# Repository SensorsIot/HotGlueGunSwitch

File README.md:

# HotGlueGunSwitch
Timer for Hot Glue Guns

Description of the project on Youtube: https://youtu.be/2SVzzAe2HBY

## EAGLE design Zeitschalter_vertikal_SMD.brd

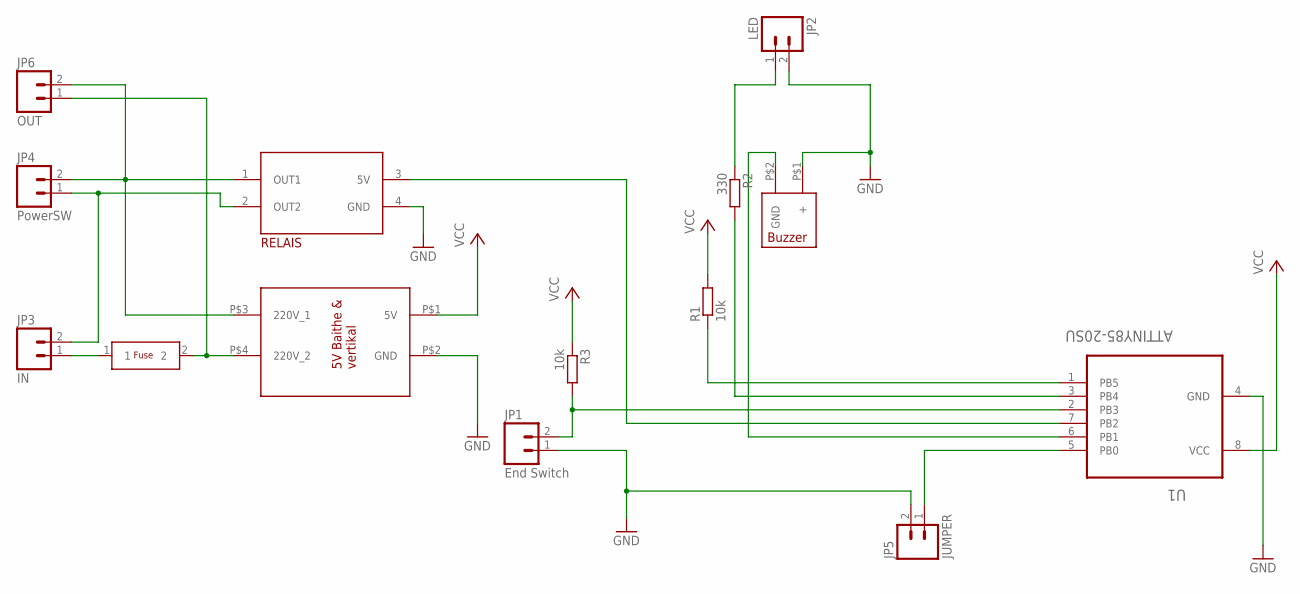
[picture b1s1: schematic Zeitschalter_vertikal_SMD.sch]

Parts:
FUSE: FUSE; FUSE_RESETABLE
JP1: End Switch; 1X02_LOCK_LONGPADS
JP2: LED; 1X02_LOCK_LONGPADS
JP3: IN; SCREWTERMINAL-5MM-2
JP4: PowerSW; 1X02_LOCK_LONGPADS
JP5: JUMPER; 1X02_LOCK_LONGPADS
JP6: OUT; SCREWTERMINAL-5MM-2
R1, R3: 10k; M1206
R2: 330; M1206
U1: ATTINY85-20SU; SOIC127P798X216-8N
U$1: NETZTEIL_VERTIKAL_5V
U$2: OMRON-G3MB-202P
U$3: BUZZER

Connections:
GND: JP1.1, JP2.2, JP5.2, U1.4 (GND), U$1.P$2 (GND), U$2.4 (GND), U$3.P$1 (+)
unnamed: FUSE.1, JP3.1
unnamed: JP4.2, JP6.2, U$1.P$3 (220V_1), U$2.1 (OUT1)
unnamed: R2.2, U1.3 (PB4)
unnamed: JP1.2, R3.2, U1.2 (PB3)
unnamed: JP5.1, U1.5 (PB0)
unnamed: FUSE.2, JP6.1, U$1.P$4 (220V_2)
unnamed: R1.1, U1.1 (PB5)
unnamed: JP2.1, R2.1
unnamed: U1.6 (PB1), U$3.P$2 (GND)
unnamed: U1.7 (PB2), U$2.3 (5V)
unnamed: JP3.2, JP4.1, U$2.2 (OUT2)
VCC: R1.2, R3.1, U1.8 (VCC), U$1.P$1 (5V)

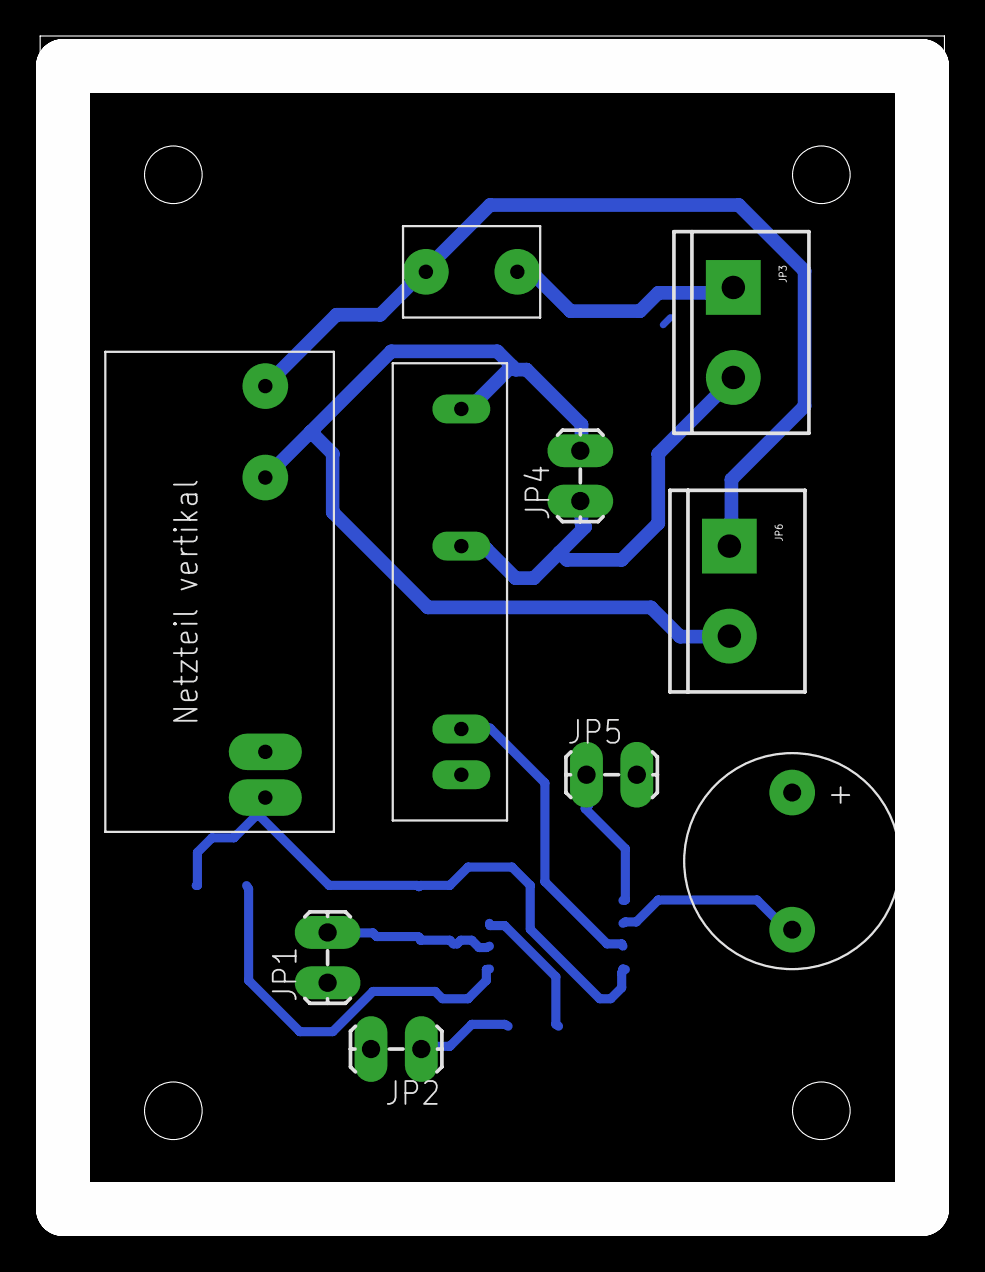
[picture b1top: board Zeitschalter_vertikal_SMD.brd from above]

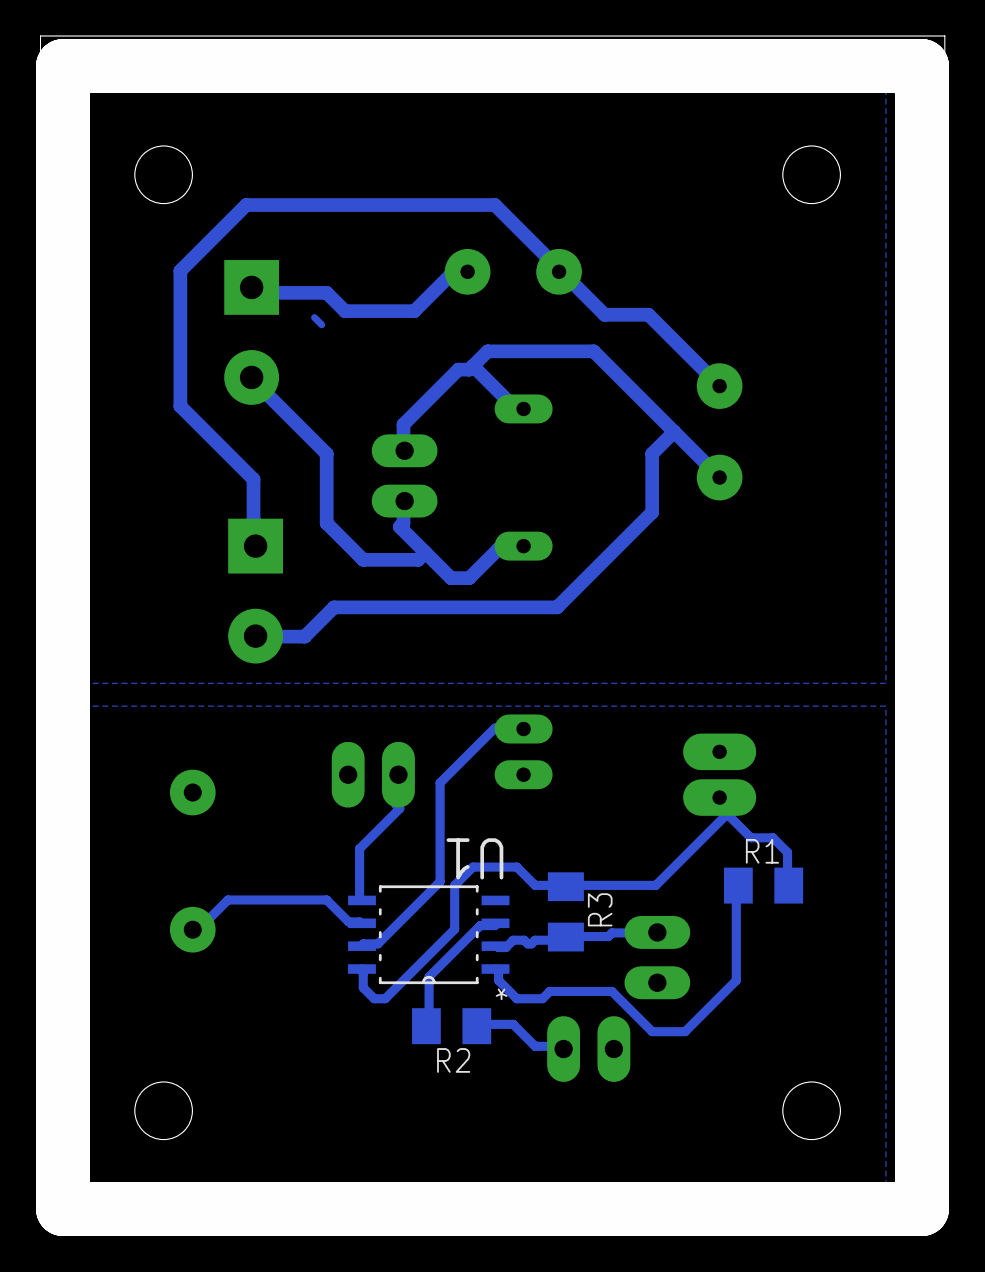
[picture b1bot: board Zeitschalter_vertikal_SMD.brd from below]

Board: 2 copper layers, 50.2 x 65.7 mm, 14 parts (4 on the bottom side), 13 nets.

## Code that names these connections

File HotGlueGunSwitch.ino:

/*
  HotGlueSwitch

  This timer turns an Hot Glue Gun or any other appliance on for a time (timer2) and switches it off afterwards.
  For Hot Glue guns a "readiness warning can be built in: after a time timer1  a beeper announces for READY_DURATION, that the temperature should be ok to start working.
  Before the timer2 switches the gun off it warns for WARNING_DURATION. During this time, pressing the button extends the time for another timer2 duration.

  It runs on an ATTINY85

  This example code is in the public domain.

  published August, 1st 2015 by Andreas Spiess
 */
 
#include <avr/io.h>
#include <EEPROM.h>


#define SW_OPEN     HIGH
#define SW_CLOSED   LOW
#define OUT_ON		HIGH
#define OUT_OFF		LOW

#define FACTOR 1000


// Pin1 RESET  #define DEBUG1 PB5 // Pin1, nur mit Fuse change

#define SWITCH PB3   // Pin2

#define LED    PB4    // Pin3
// Pin4 GND
#define PROGRAMMER PB0    // Pin5
#define BUZZER PB1   // Pin6
#define RELAIS PB2    // Pin7
// Pin8 VCC

const int timer2 = 600;   // 600 sec = 10min
const int timer1 = 140; // 140 sec (until glue is hot enough;
const int WARNING_DURATION = 60;  // 60sec;
const int READY_DURATION = 3;   // 3 sec

byte status = 1;
long timeStat;

void setup() {
  pinMode(SWITCH, INPUT_PULLUP);
  pinMode(LED, OUTPUT);
  pinMode(PROGRAMMER, INPUT);
  pinMode(BUZZER, OUTPUT);
  pinMode(RELAIS, OUTPUT);
  digitalWrite(SWITCH, HIGH); //
  digitalWrite(LED, OUT_OFF); //
  digitalWrite(BUZZER, OUT_OFF); //
  digitalWrite(RELAIS, OUT_ON); //
  timeStat = millis();
  delay(200);

}


void loop () {
  switch (status) {

    case 1:
      // Appliance on
      digitalWrite(RELAIS, OUT_ON);
      digitalWrite(LED, OUT_ON);
      if (timeOut(timeStat, timer1))  status = 5; // Appliance ready
      break;

    case 2:
      // Warning
      beep(200);
      smartDelay(2000);
      if (keyPressed())  status = 3;
      if (timeOut(timeStat, timer2)) status = 4;  // Appliance off
      break;

    case 3:
      // Time Extension
      timeStat = millis();   // reset timer to start duration over
      for (int ii = 0; ii < 3; ii++) {   ///three beeps for confirmation
        beep(100);
        delay(100);
      }
      timeStat = millis();
      status = 6;
      break;

    case 4:
      // Appliance off
      digitalWrite(RELAIS, OUT_OFF);
      digitalWrite(LED, OUT_OFF);
      digitalWrite(BUZZER, OUT_OFF);
      while (1 == 1);  // wait forever
      break;

    case 5:
      // Appliance ready
      digitalWrite(RELAIS, OUT_ON);
      digitalWrite(LED, OUT_ON);
      beep(200);
      smartDelay(100);
      if (timeOut(timeStat, (timer1 + READY_DURATION))) status = 6;
      if (keyPressed()) status = 3;   // time extension
      break;

    case 6:
      // Status after Appliance ready: Appliance still on, but no more warning for readiness
      digitalWrite(RELAIS, OUT_ON);
      digitalWrite(LED, OUT_ON);
      if (timeOut(timeStat, timer2 - WARNING_DURATION)) status = 2;
      if (keyPressed()) status = 3;   // time extension
      break;

    default:  // should never happen...
      status = 1;
      break;
  }
  delay(100);
}

boolean timeOut(long zeitEin, long dauer) {
  boolean timeOut = false;
  if (millis() - zeitEin >= dauer * FACTOR) {
    timeOut = true;
  }
  return timeOut;
}


boolean keyPressed() {
  bool tt = false;
  if (digitalRead(SWITCH) == SW_CLOSED) {
    tt = true;
    while (digitalRead(SWITCH) == SW_CLOSED) {
      delay(50);
    }
  }
  return tt;
}

void smartDelay(int delay) {
  unsigned long start = millis();
  while (millis() - start < delay) {
    if (digitalRead(SWITCH) == SW_CLOSED)  break;
  }
}


void beep(int dauer) {
  digitalWrite(BUZZER, OUT_ON);
  digitalWrite(LED, OUT_OFF);
  smartDelay(dauer);
  digitalWrite(BUZZER, OUT_OFF);
  digitalWrite(LED, OUT_ON);
}

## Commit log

2015-08-12 :neckbeard: Added .gitattributes & .gitignore files
2015-08-12 Timer for Hot Glue Guns
    Description of the project on Youtube: https://youtu.be/2SVzzAe2HBY
2015-09-20 New code
    The first version was unfortunately an untested experimental version.
    This one should work now

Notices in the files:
parts and their libraries:
SparkFun-Connectors: Licensing: Creative Commons ShareAlike 4.0 International - https://creativecommons.org/licenses/by-sa/4.0
